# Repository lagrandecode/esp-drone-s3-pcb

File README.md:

# ESP-Drone S3: PCB-frame micro quadcopter

A 4-layer, 86.5 × 86.5 mm flight controller that is also the drone frame. It uses
brushed 720 motors clamped in rubber motor rings, runs Espressif's open-source
[ESP-Drone](https://github.com/espressif/esp-drone) firmware unmodified, and is
flown from a phone over Wi-Fi.

## Folder contents

| Path | What it is |
| --- | --- |
| `production/esp_drone_s3_gerbers.zip` | Upload this to JLCPCB as the PCB |
| `production/esp_drone_s3_bom.csv` | Bill of materials with LCSC part numbers (JLCPCB format) |
| `production/esp_drone_s3_bom_lcsc_shopping.csv` | Same parts for buying loose from LCSC (three capacitors swapped for in-stock cut-tape equivalents) |
| `production/esp_drone_s3_assembly_guide.html` | Interactive placement guide for hand assembly |
| `production/esp_drone_s3_cpl.csv` | Pick-and-place file with JLCPCB rotation and centroid corrections applied |
| `production/esp_drone_s3_netlist.csv` | Every net and the pins it connects (the design has no schematic sheet) |
| `production/render_*.png` | 3D renders |
| `kicad/` | KiCad 10 project. Open `esp_drone_s3.kicad_pro` |
| `tools/` | Scripts that generate the whole board (`tools/pipeline.sh`, then `tools/fab.py`) |

## Hardware summary

- **MCU:** ESP32-S3-WROOM-1-N8. The antenna overhangs the front edge, as Espressif recommends.
- **IMU:** MPU-6050 at the centre of the frame, oriented to match ESP-Drone's axis remapping.
- **Power:** 1S LiPo on solder pads. A load-sharing power path feeds the AP2112K 3.3 V regulator from USB or the battery. A TP4056 charges the battery at 400 mA over USB-C. A slide switch turns the electronics on and off (charging works with the switch off).
- **Motor drivers:** four AO3400A low-side MOSFETs with SS34 flyback diodes and gate pull-downs, so the motors stay off during boot.
- **Board:** 4 layers, 1.6 mm. Inner layer 1 is a solid ground plane. Inner layer 2 is a solid battery (VBAT) plane that runs into every arm, so motor current never goes through thin traces.
- **Also on board:** battery voltage sense (1:2 divider on GPIO2), status LEDs, charge and full LEDs, BOOT and RESET buttons, and native USB for flashing.
- **Geometry:** motors are 70 mm apart (99 mm diagonal), which fits 55 mm props (65 mm maximum).

The pin map is identical to ESP-Drone's default for ESP32-S3 (`TARGET_ESP32_S2_DRONE_V1_2`):

| Function | GPIO | | Function | GPIO |
| --- | --- | --- | --- | --- |
| M1 front-right (CCW) | 5 | | MPU-6050 SDA / SCL | 11 / 10 |
| M2 rear-right (CW) | 6 | | MPU-6050 INT | 12 |
| M3 rear-left (CCW) | 3 | | Battery ADC | 2 |
| M4 front-left (CW) | 4 | | LED red / green / blue | 8 / 9 / 7 |
| USB D- / D+ | 19 / 20 | | BOOT | 0 |

## Ordering at JLCPCB

1. Go to jlcpcb.com and upload `production/esp_drone_s3_gerbers.zip`.
   - Layers: **4** (detected automatically). Thickness **1.6 mm**. Everything else can stay at the defaults.
   - Surface finish: ENIG is recommended for the QFN IMU; lead-free HASL also works.
   - Remove order number: choose **Specify a location**. A `JLCJLCJLCJLC` marker is already on the bottom silkscreen.
2. Turn on **PCB Assembly**: top side, any quantity (2 is the minimum).
   - If JLCPCB asks about edge rails for the irregular outline, pick **Added by JLCPCB** on the **left and right** sides. The module overhangs the front edge, so the front has to stay free.
3. Upload `esp_drone_s3_bom.csv` and `esp_drone_s3_cpl.csv`.
4. On the placement preview page, check the parts against the render above. The rotations are already corrected, but this preview is your last free check.
   - The ESP32 antenna points to the front, past the board edge.
   - The USB-C opening faces outward at the rear.
   - The MPU-6050 pin-1 dot is at the lower right of the chip.
5. Expect about 8 "extended part" setup fees (ESP32-S3 module, MPU-6050, TP4056, AP2112K, USB-C, green LED, blue LED, slide switch). Everything else is a basic part.

Stock was checked on 2026-11-04. The tightest parts were ESP32-S3-WROOM-1-N8 (C2913198, about 4,600 in stock) and MPU-6050 (C24112, about 6,600). If either sells out, the BOM page will flag it before you pay.

## Parts to buy separately

- 4 × 720 brushed coreless motors (7 × 20 mm), 2 CW and 2 CCW
- 4 × rubber motor rings for 7 mm motors (11 mm outer diameter, sold as "716/720 motor rubber ring")
- 55 mm propellers: 2 × A (CW) and 2 × B (CCW), matched to the motor shaft size
- 1S LiPo, 300 to 500 mAh, 20C or higher

## Assembly

1. **Motors:** push each motor, inside its rubber ring, into the clamp ring. The silkscreen shows the layout and spin direction: M1 front-right CCW, M2 rear-right CW, M3 rear-left CCW, M4 front-left CW.
2. **Motor wires:** solder each motor's positive lead to the `+` pad on its arm and the negative lead to `-`. Usually red/blue wires are CW motors and white/black are CCW. Before fitting props, confirm each motor spins in the direction of the arrow on its ring.
3. **Battery:** solder the leads to **BAT+ / BAT-** (also labelled on the bottom), or solder on a pigtail with your battery's connector. **There is no reverse-polarity protection.** Connecting the battery backwards will destroy the charger and regulator. Stick the battery to the centre of the bottom side with foam tape.
4. **Props:** fit the A props on M2 and M4, and the B props on M1 and M3.

## Firmware (no configuration changes needed)

```sh
# ESP-IDF release/v5.5 environment
git clone https://github.com/espressif/esp-drone.git && cd esp-drone
idf.py set-target esp32s3
idf.py build
# slide the power switch to ON, plug in USB-C
idf.py -p /dev/cu.usbmodem* flash monitor
```

The ESP32 is only powered when the slide switch is **ON**, including when it's on USB. If the port doesn't appear, hold **BOOT**, tap **RST**, then release **BOOT**.

To fly, install the ESP-Drone app (Android or iOS) and join the Wi-Fi network `ESP-DRONE_<mac>` with password `12345678`.

## First power-up (props off)

1. **USB only:** plug in USB-C with the switch ON. The ESP-Drone LED sequence should start, and the 3V3 rail should read 3.3 V.
2. **Charging:** with the battery connected and USB in, the CHG LED is lit while charging and the FULL LED lights when charging finishes.
3. **Motors:** run a motor test from the app with the props still off.

## Verification status

What has been checked:

- **KiCad design-rule check:** 0 errors, 0 unconnected items. This covers clearances, hole spacing, courtyard overlaps, and plane connectivity, and uses JLCPCB-standard rules (0.15 mm minimum track and space, 0.3 mm drills, no extra-cost options).
- **Firmware match:** every GPIO, the IMU address (0x68), the IMU axis orientation, LED polarity, the battery divider ratio, and the motor numbering and spin directions were checked against the esp-drone source code.
- **Datasheets:** the MPU-6050 pin handling follows the datasheet in the esp-drone repo. The TP4056, AP2112K, and USB-C CC resistors follow their standard reference circuits.
- **Placement file:** rotation and centroid for every part were computed by matching KiCad pads against JLCPCB's own footprint for that LCSC number (`production/jlc_corrections.txt`).

What hasn't been checked:

- The board has not been physically built or flown.
- JLCPCB's human DFM review still runs after you upload.
- There is no schematic sheet. The circuit is defined in `tools/design.py` and exported as `production/esp_drone_s3_netlist.csv`.

## Regenerating

Requires KiCad 10, Java 21+ (Homebrew `openjdk@25` path is set in `tools/route.py`), and shapely in KiCad's Python:

```sh
<KiCad python> -m pip install --target tools/pylib "shapely<2.1"
tools/pipeline.sh                                    # place, autoroute (Freerouting 2.5, auto-downloaded), finish, DRC
PYTHONPATH=tools/pylib <KiCad python> tools/fab.py  # BOM, CPL, Gerbers, renders
```

Edit `tools/design.py` to change parts, nets, or placement.

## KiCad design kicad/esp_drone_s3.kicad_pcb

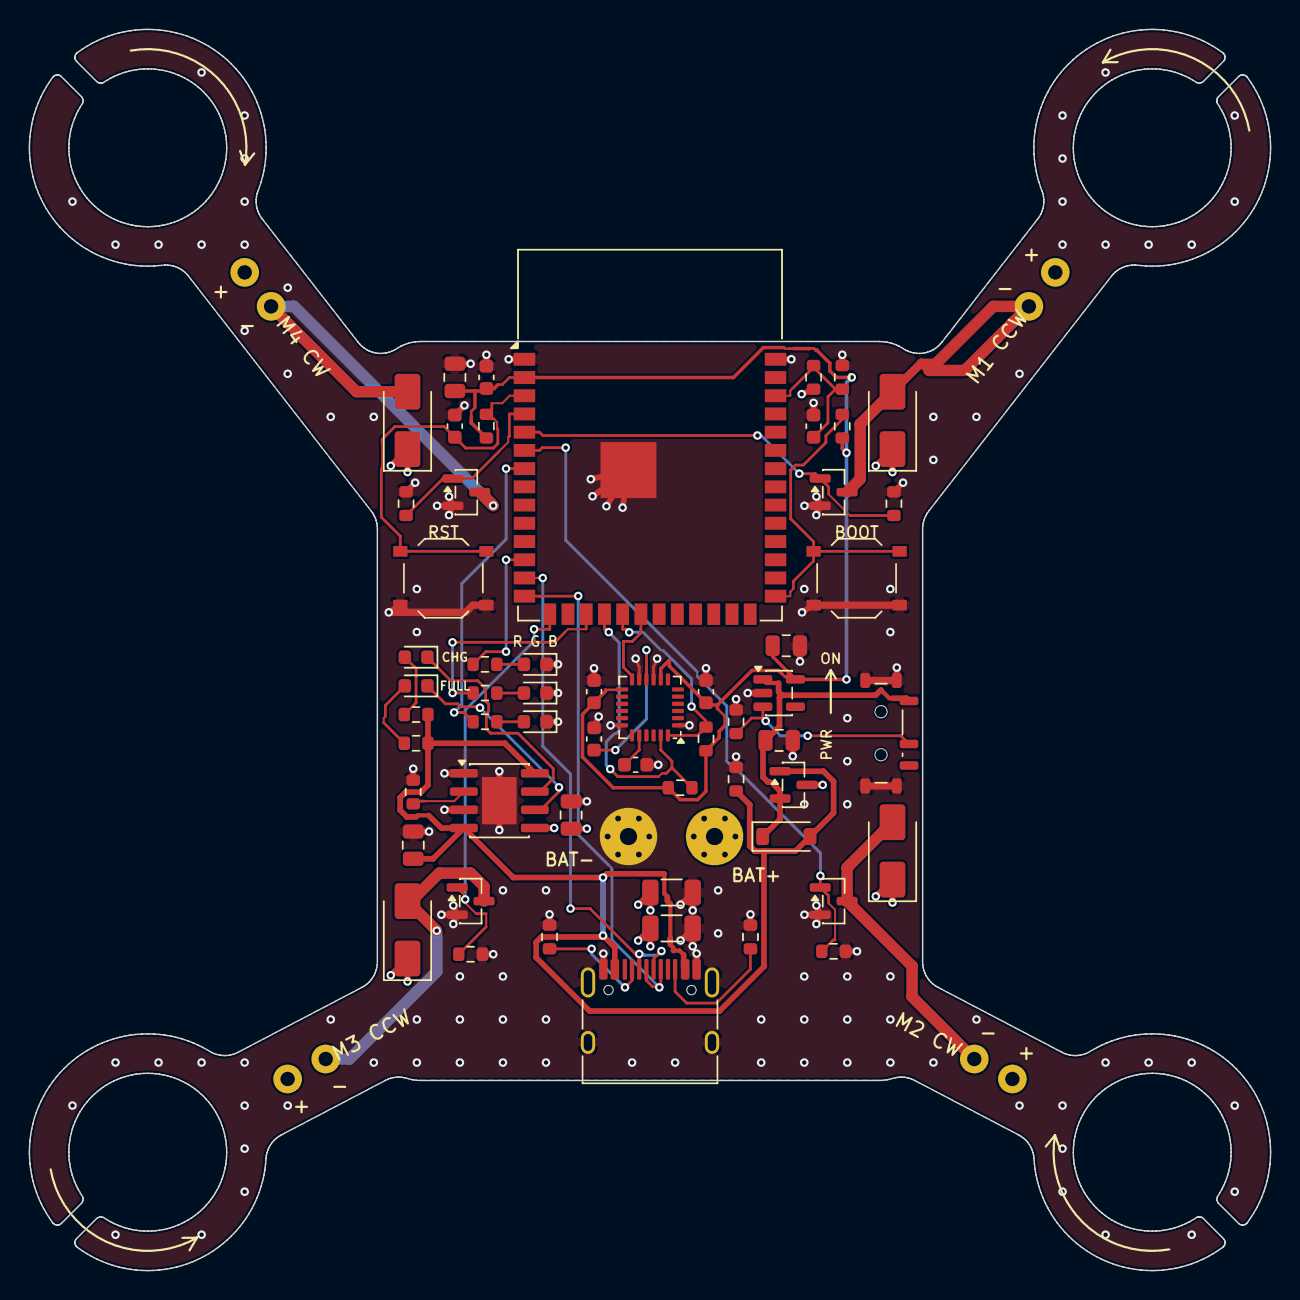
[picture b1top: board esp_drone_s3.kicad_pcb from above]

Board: 4 copper layers, 86.5 x 86.5 mm, 62 parts (0 on the bottom side), 37 nets.

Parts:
BT1: BATTERY; BATTERY_PADS
C1: 1uF; C_0603_1608Metric
C2: 22uF; C_0805_2012Metric
C3, C10, C12, C14: 100nF; C_0603_1608Metric
C4, C5, C6, C7: 10uF; C_0805_2012Metric
C8, C9: 47uF; C_1206_3216Metric
C11: 10nF; C_0603_1608Metric
C13: 2.2nF; C_0603_1608Metric
D1, D2, D3, D4: SS34; D_SMA
D5: B5819W; D_SOD-123
J1: USB-C; USB_C_Receptacle_HRO_TYPE-C-31-M-12
LED1, LED4: RED; LED_0603_1608Metric
LED2, LED5: GREEN; LED_0603_1608Metric
LED3: BLUE; LED_0603_1608Metric
M1, M2, M3, M4: MOTOR; MOTOR_PADS
Q1, Q2, Q3, Q4: AO3400A; SOT-23
Q5: AO3401A; SOT-23
R1, R2: 5.1k; R_0603_1608Metric
R3: 3k; R_0603_1608Metric
R4, R5: 1k; R_0603_1608Metric
R6: 470R; R_0603_1608Metric
R7, R8: 100R; R_0603_1608Metric
R9, R10, R16, R17, R18, R19: 10k; R_0603_1608Metric
R11, R12: 4.7k; R_0603_1608Metric
R13, R14, R15, R20: 100k; R_0603_1608Metric
SW1: BOOT; SW_Push_1P1T_XKB_TS-1187A
SW2: RESET; SW_Push_1P1T_XKB_TS-1187A
SW3: POWER; SW_SPDT_Shouhan_MSK12C02
U1: ESP32-S3-WROOM-1-N8; ESP32-S3-WROOM-1
U2: MPU-6050; InvenSense_QFN-24_4x4mm_P0.5mm
U3: TP4056; SOIC-8-1EP_3.9x4.9mm_P1.27mm_EP2.41x3.3mm
U4: AP2112K-3.3; SOT-23-5

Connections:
3V3: C2.1, C3.1, C5.1, C10.1, C11.1, R9.1, R10.1, R11.1, R12.1, U1.2, U2.8, U2.13, U4.5
BOOT: R10.2, SW1.1, U1.27
CC1: J1.A5, R1.1
CC2: J1.B5, R2.1
CHG_CHRG: LED4.1, U3.7
CHG_STDBY: LED5.1, U3.6
EN: C1.1, R9.2, SW2.1, U1.3
GND: BT1.2, C1.2, C2.2, C3.2, C4.2, C5.2, C6.2, C7.2, C8.2, C9.2, C10.2, C11.2, C12.2, C13.2, C14.2, J1.A1, J1.A12, J1.B1, J1.B12, J1.SH, LED1.1, LED2.1, LED3.1, Q1.2, Q2.2, Q3.2, Q4.2, R1.2, R2.2, R3.2, R14.2, R15.2, R16.2, R17.2, R18.2, R19.2, R20.2, SW1.2, SW2.2, SW3.SH, U1.1, U1.40, U1.41, U2.1, U2.9, U2.11, U2.18, U3.1, U3.3, U3.9, U4.2
I2C_SCL: R12.2, U1.18, U2.23
I2C_SDA: R11.2, U1.19, U2.24
IMU_INT: U1.20, U2.12
LDO_EN: R20.1, SW3.2, U4.3
LED4_A: LED4.2, R4.1
LED5_A: LED5.2, R5.1
LED_B: R8.1, U1.7
LED_B_A: LED3.2, R8.2
LED_G: R7.1, U1.17
LED_G_A: LED2.2, R7.2
LED_R: R6.1, U1.12
LED_R_A: LED1.2, R6.2
MOT1_N: D1.2, M1.2, Q1.3
MOT1_PWM: Q1.1, R16.1, U1.5
MOT2_N: D2.2, M2.2, Q2.3
MOT2_PWM: Q2.1, R17.1, U1.6
MOT3_N: D3.2, M3.2, Q3.3
MOT3_PWM: Q3.1, R18.1, U1.15
MOT4_N: D4.2, M4.2, Q4.3
MOT4_PWM: Q4.1, R19.1, U1.4
MPU_CPOUT: C13.1, U2.20
MPU_REGOUT: C12.1, U2.10
TP_PROG: R3.1, U3.2
USB_DN: J1.A7, J1.B7, U1.13
USB_DP: J1.A6, J1.B6, U1.14
VBAT: BT1.1, C7.1, C8.1, C9.1, D1.1, D2.1, D3.1, D4.1, M1.1, M2.1, M3.1, M4.1, Q5.3, R13.1, U3.5
VBAT_ADC: C14.1, R13.2, R14.1, U1.38
VBUS: C6.1, D5.2, J1.A4, J1.A9, J1.B4, J1.B9, Q5.1, R4.2, R5.2, R15.1, U3.4, U3.8
VSYS: C4.1, D5.1, Q5.2, SW3.1, U4.1

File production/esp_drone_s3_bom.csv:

Comment,Designator,Footprint,LCSC Part #
1uF,C1,C_0603_1608Metric,C15849
22uF,C2,C_0805_2012Metric,C45783
100nF,"C3,C10,C12,C14",C_0603_1608Metric,C14663
10uF,"C4,C5,C6,C7",C_0805_2012Metric,C15850
47uF,"C8,C9",C_1206_3216Metric,C96123
10nF,C11,C_0603_1608Metric,C57112
2.2nF,C13,C_0603_1608Metric,C1604
SS34,"D1,D2,D3,D4",D_SMA,C8678
B5819W,D5,D_SOD-123,C8598
USB-C,J1,USB_C_Receptacle_HRO_TYPE-C-31-M-12,C165948
RED,"LED1,LED4",LED_0603_1608Metric,C2286
GREEN,"LED2,LED5",LED_0603_1608Metric,C12624
BLUE,LED3,LED_0603_1608Metric,C2288
AO3400A,"Q1,Q2,Q3,Q4",SOT-23,C20917
AO3401A,Q5,SOT-23,C15127
5.1k,"R1,R2",R_0603_1608Metric,C23186
3k,R3,R_0603_1608Metric,C4211
1k,"R4,R5",R_0603_1608Metric,C21190
470R,R6,R_0603_1608Metric,C23179
100R,"R7,R8",R_0603_1608Metric,C22775
10k,"R9,R10,R16,R17,R18,R19",R_0603_1608Metric,C25804
4.7k,"R11,R12",R_0603_1608Metric,C23162
100k,"R13,R14,R15,R20",R_0603_1608Metric,C25803
BOOT,SW1,SW_Push_1P1T_XKB_TS-1187A,C318884
RESET,SW2,SW_Push_1P1T_XKB_TS-1187A,C318884
POWER,SW3,SW_SPDT_Shouhan_MSK12C02,C431540
ESP32-S3-WROOM-1-N8,U1,ESP32-S3-WROOM-1,C2913198
MPU-6050,U2,InvenSense_QFN-24_4x4mm_P0.5mm,C24112
TP4056,U3,SOIC-8-1EP_3.9x4.9mm_P1.27mm_EP2.41x3.3mm,C16581
AP2112K-3.3,U4,SOT-23-5,C51118
